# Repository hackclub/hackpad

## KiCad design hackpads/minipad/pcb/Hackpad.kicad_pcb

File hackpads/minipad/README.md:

# Minipad
My first time experimenting with PCB, keyboards, firmware and everything that comes along with it.
To keep things simple, I created a simple 4 switch grid (with one rotary encoder) direct wired to the microcontroller.
The case is another simple design, with a rectangular shape with curved corners, with some empty space to add some stickers or similar.

# BOM
- 3x Cherry MX switches
- 1x EC11 Encoder
- 1x PCB
- 1x Xiao Seeed RP2040
- 3x Blank DSA Key Caps
- 1x sticker to put on top

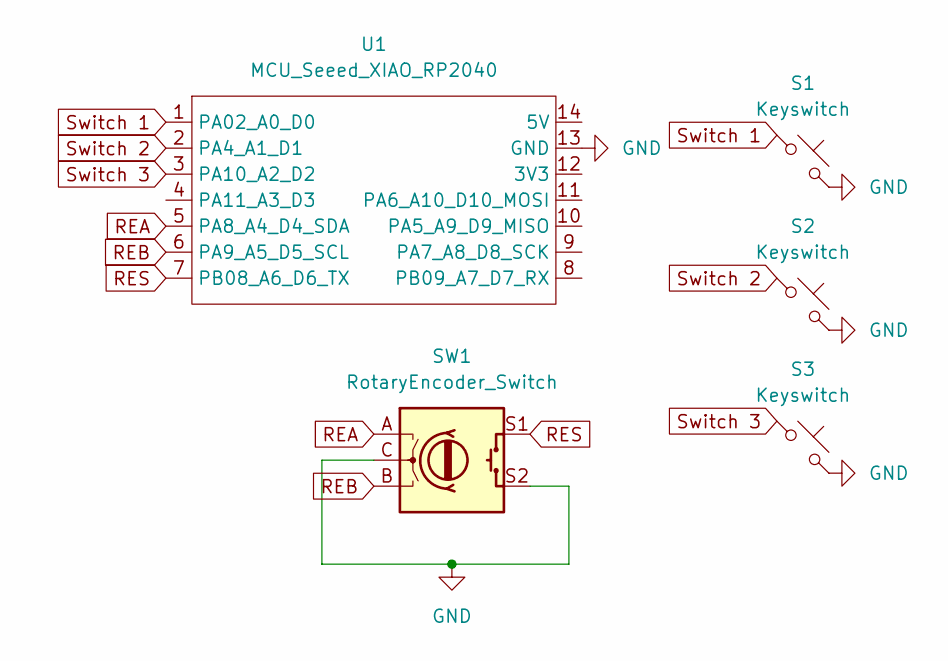
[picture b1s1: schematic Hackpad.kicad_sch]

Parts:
S1, S2, S3: Keyswitch; MX_PCB_1.00u
SW1: RotaryEncoder_Switch; Encoder_EC11_MX
U1: MCU_Seeed_XIAO_RP2040; Seeed_XIAO_RP2040

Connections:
GND: S1.2, S2.2, S3.2, SW1.C, SW1.S2, U1.13 (GND)
REA: SW1.A, U1.5 (PA8_A4_D4_SDA)
REB: SW1.B, U1.6 (PA9_A5_D5_SCL)
RES: SW1.S1, U1.7 (PB08_A6_D6_TX)
Switch 1: S1.1, U1.1 (PA02_A0_D0)
Switch 2: S2.1, U1.2 (PA4_A1_D1)
Switch 3: S3.1, U1.3 (PA10_A2_D2)

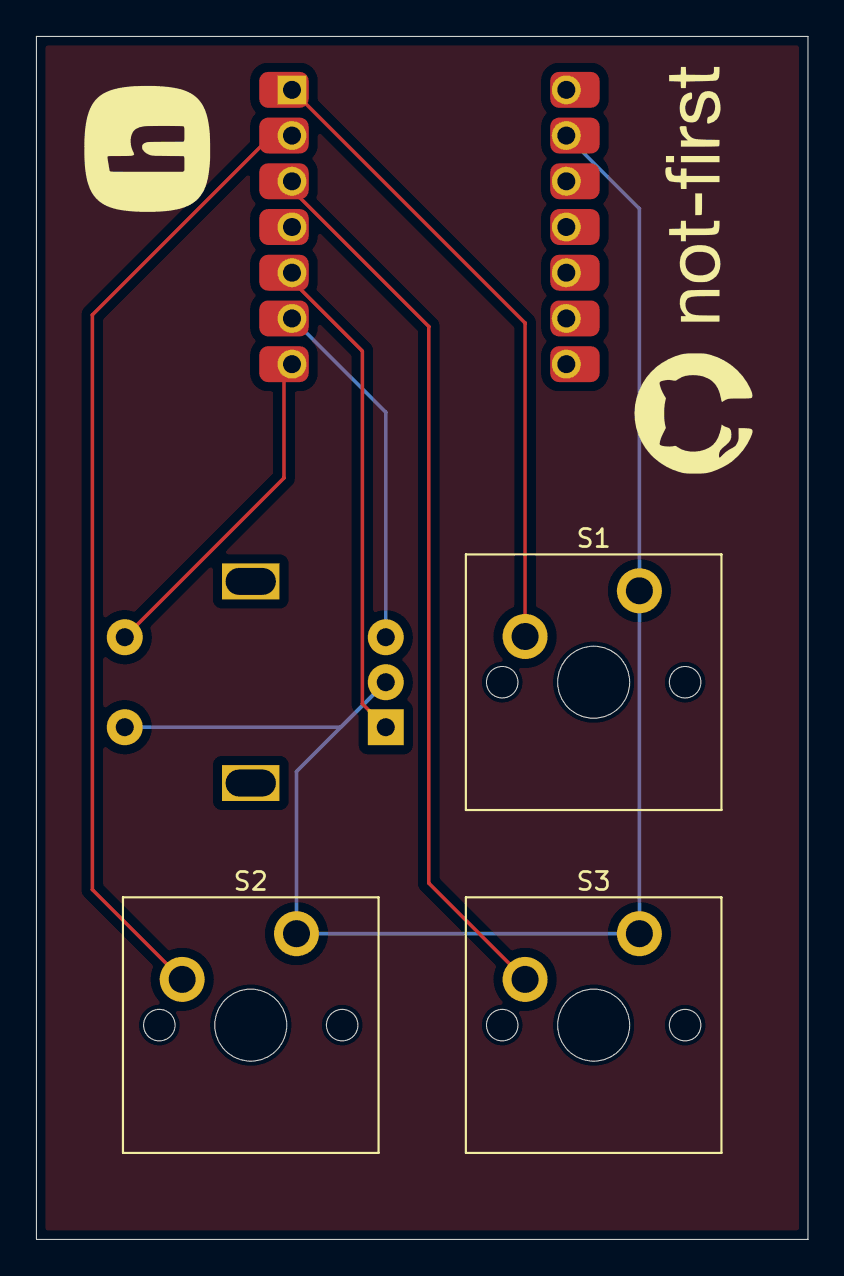
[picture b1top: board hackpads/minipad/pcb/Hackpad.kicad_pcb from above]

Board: 2 copper layers, 42.9 x 66.8 mm, 5 parts (0 on the bottom side), 7 nets.

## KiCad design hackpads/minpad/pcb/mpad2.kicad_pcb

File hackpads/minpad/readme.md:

# Minpad

A simple 2x3 macro pad with a display!

Designing a case was difficult, as I barely have any cad experience, but the PCB was really fun! I'll definitely look into more projects like this later on.

## PCB

Front and back of the PCB, the whole board uses a fill zone.

## Bill of materials

| Component                  | Amount |
|----------------------------|--------|
| PCB                        | 1      |
| Cherry MX Switches         | 6      |
| Seeduino Xiao RP2040       | 1      |
| WS28128 LED                | 1      |
| Through-hole 1N4148 Diodes | 6      |
| OLED 128x32                | 1      |
| Keycaps                    | 6      |

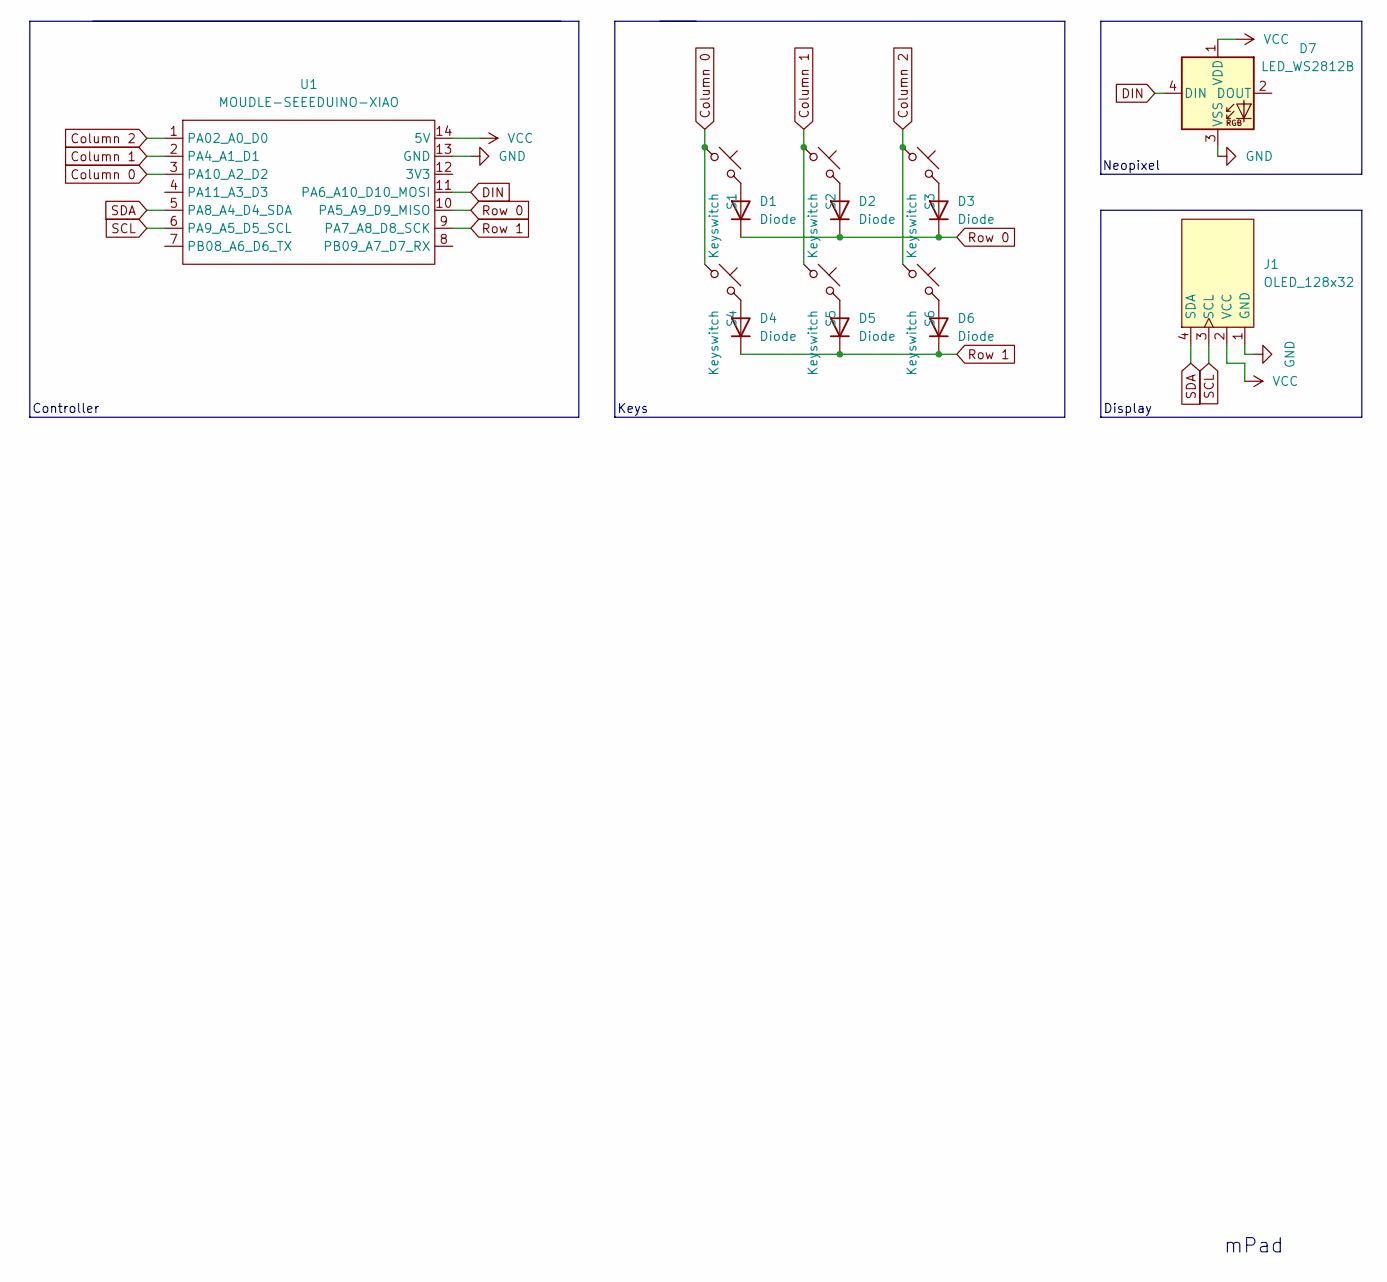
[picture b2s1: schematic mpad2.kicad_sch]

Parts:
D1, D2, D3, D4, D5, D6: Diode; Diode_DO-35
D7: LED_WS2812B
J1: OLED_128x32
S1, S2, S3, S4, S5, S6: Keyswitch; MX_PCB_1.00u
U1: MOUDLE-SEEEDUINO-XIAO; Seeed_XIAO_RP2040

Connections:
Column 0: S1.1, S4.1, U1.3 (PA10_A2_D2)
Column 1: S2.1, S5.1, U1.2 (PA4_A1_D1)
Column 2: S3.1, S6.1, U1.1 (PA02_A0_D0)
DIN: D7.4 (DIN), U1.11 (PA6_A10_D10_MOSI)
GND: D7.3 (VSS), J1.1 (GND), U1.13 (GND)
unnamed: D1.2 (A), S1.2
unnamed: D2.2 (A), S2.2
unnamed: D3.2 (A), S3.2
unnamed: D4.2 (A), S4.2
unnamed: D5.2 (A), S5.2
unnamed: D6.2 (A), S6.2
Row 0: D1.1 (K), D2.1 (K), D3.1 (K), U1.10 (PA5_A9_D9_MISO)
Row 1: D4.1 (K), D5.1 (K), D6.1 (K), U1.9 (PA7_A8_D8_SCK)
SCL: J1.3 (SCL), U1.6 (PA9_A5_D5_SCL)
SDA: J1.4 (SDA), U1.5 (PA8_A4_D4_SDA)
VCC: D7.1 (VDD), J1.2 (VCC), U1.14 (5V)

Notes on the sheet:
Neopixel
Controller
mPad
Display
Keys

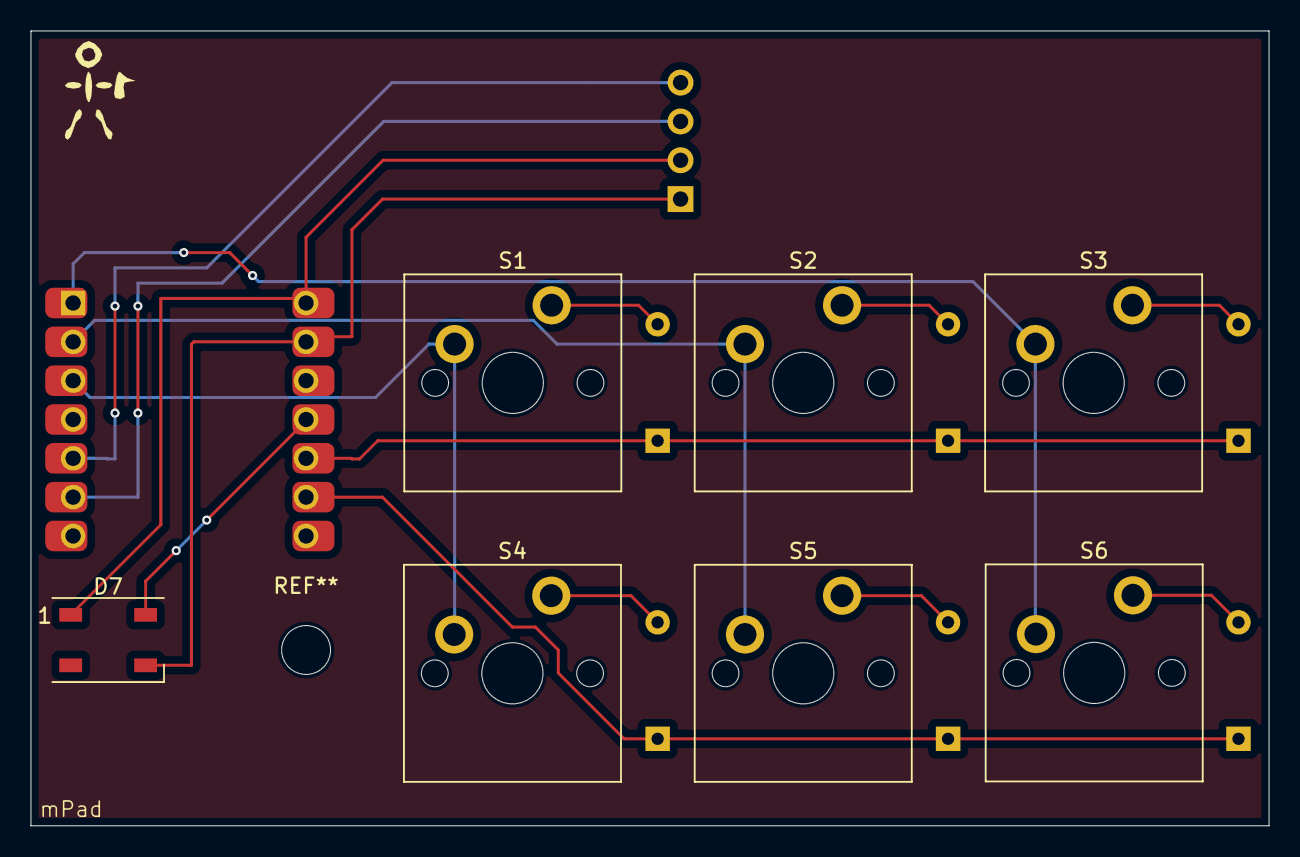
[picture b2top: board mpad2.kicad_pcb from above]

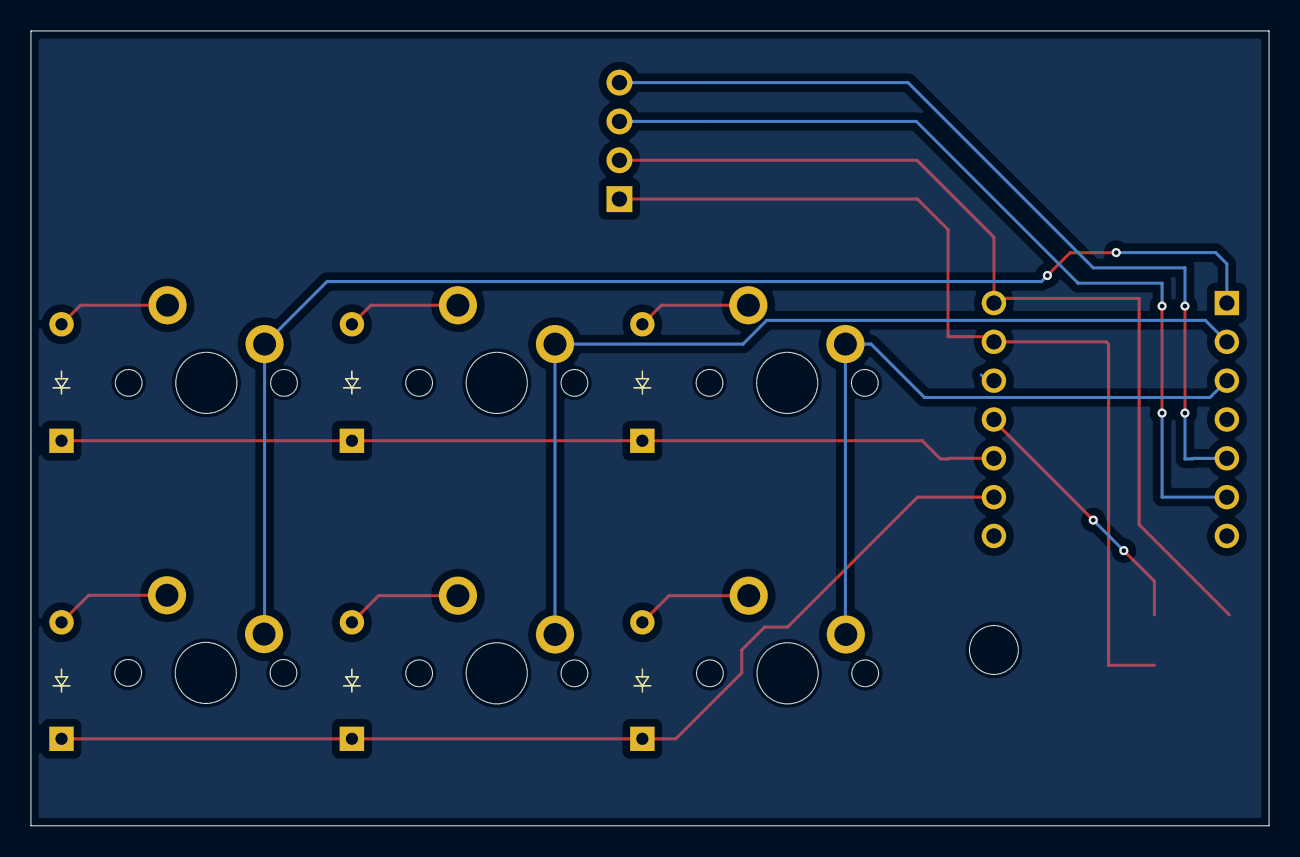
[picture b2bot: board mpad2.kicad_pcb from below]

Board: 2 copper layers, 81.0 x 52.0 mm, 15 parts (6 on the bottom side), 16 nets.

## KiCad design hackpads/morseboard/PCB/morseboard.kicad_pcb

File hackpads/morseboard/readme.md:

# Morseboard

My hackpad keyboard is a keyboard that types in morse code. The rotary encoder is for volume. I was inspired to do this because I kept making smaller and smaller keyboards, and this is the next step in my journey. Maybe one day, I'll make a 1-key keyboard. The reason I chose to use morse code, was because I coincidentally was learning it for fun. This was also my first time truly designing my own keyboard with my previous keyboards just being half of a pre-built split keyboard, so I had to learn how to use real CAD tools.

## Features
- Rotary Encoder
- Morse Code!!
- Screen

## Schematics

## PCB

## Assembly

## BOM

| Qty | Part Name               |
|-----|-------------------------|
| 1   | Rotary Encoder          |
| 6   | Cherry MX Switches      |
| 6   | DSA Keycaps             |
| 1   | 0.91 inch OLED displays |
| 7   | SK6812 MINI-E LEDs      |
| 1   | Seeed XIAO RP2040       |
| 6   | THT 1N4148 Diodes       |
| 1   | Case (3d-printed)       |
| 5   | PCB                     |

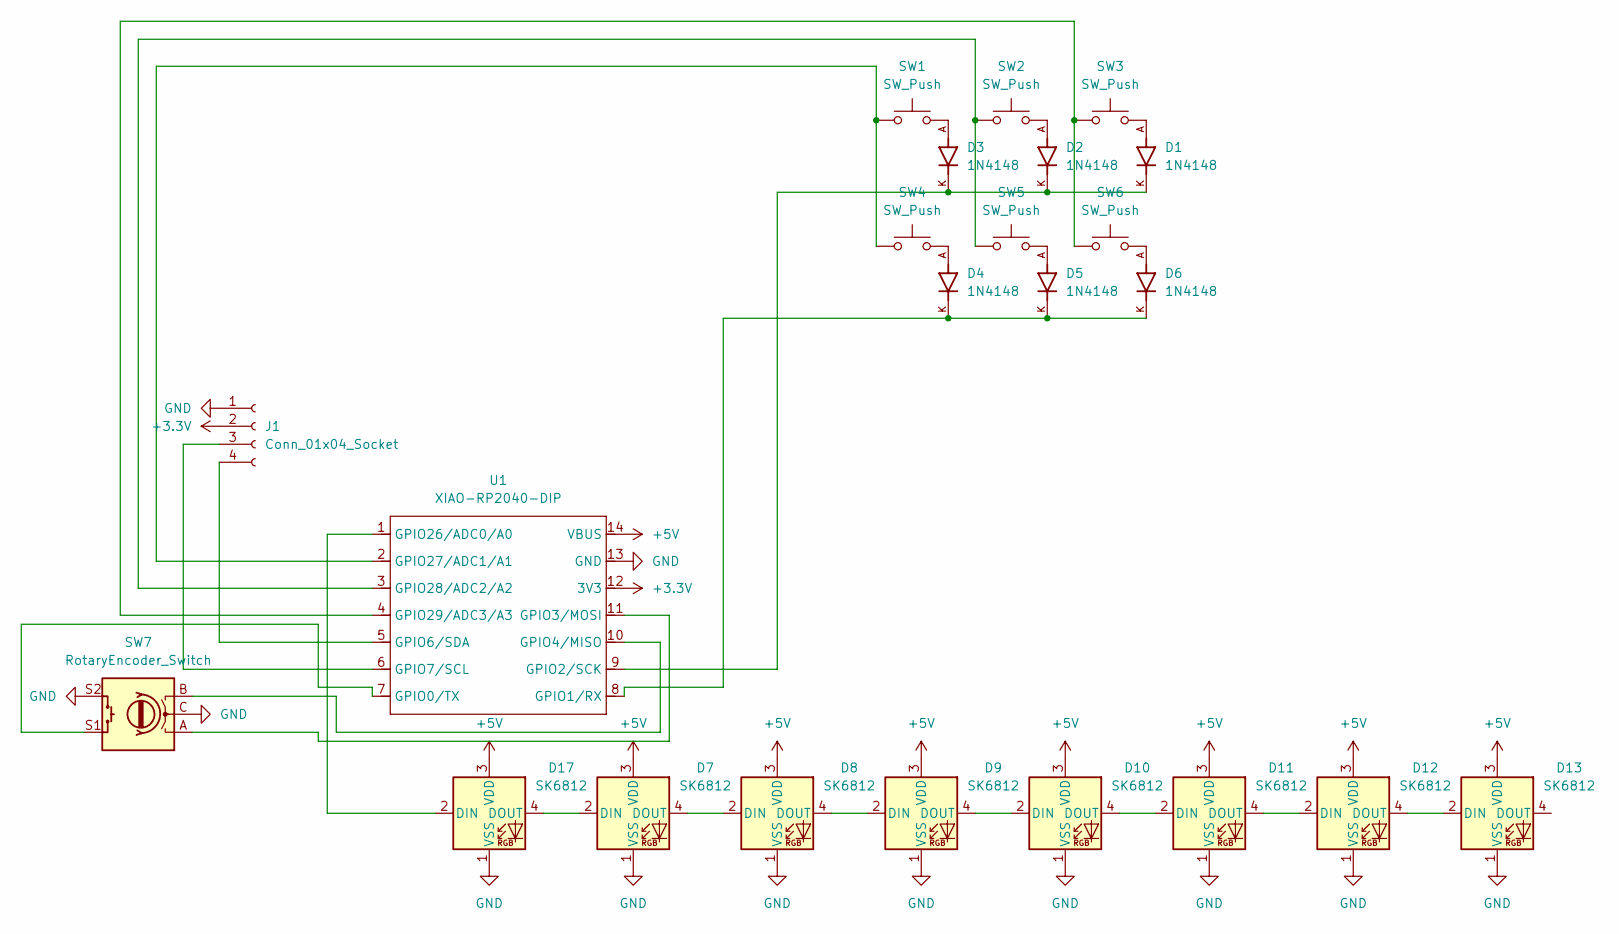
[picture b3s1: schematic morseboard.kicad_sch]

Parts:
D1, D2, D3, D4, D5, D6: 1N4148; DIOAD753W49L380D172B; PARTREV 5; DigiKey_Part_Number 1N4148FS-ND
D7, D8, D9, D10, D11, D12, D13, D17: SK6812; LED_SK6812_PLCC4_5.0x5.0mm_P3.2mm
J1: Conn_01x04_Socket; SSD1306-0.91-OLED-4pin-128x32
SW1, SW2, SW3, SW4, SW5, SW6: SW_Push; SW_Cherry_MX_1.00u_PCB
SW7: RotaryEncoder_Switch; RotaryEncoder_Alps_EC11E-Switch_Vertical_H20mm_CircularMoun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
U1: XIAO-RP2040-DIP

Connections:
+3.3V: J1.2, U1.12 (3V3)
+5V: D7.3 (VDD), D8.3 (VDD), D9.3 (VDD), D10.3 (VDD), D11.3 (VDD), D12.3 (VDD), D13.3 (VDD), D17.3 (VDD), U1.14 (VBUS)
GND: D7.1 (VSS), D8.1 (VSS), D9.1 (VSS), D10.1 (VSS), D11.1 (VSS), D12.1 (VSS), D13.1 (VSS), D17.1 (VSS), J1.1, SW7.C, SW7.S2, U1.13 (GND)
unnamed: D1.A, SW3.2
unnamed: D2.A, SW2.2
unnamed: D3.A, SW1.2
unnamed: D4.A, SW4.2
unnamed: D5.A, SW5.2
unnamed: D6.A, SW6.2
unnamed: D7.4 (DOUT), D8.2 (DIN)
unnamed: D8.4 (DOUT), D9.2 (DIN)
unnamed: D9.4 (DOUT), D10.2 (DIN)
unnamed: D10.4 (DOUT), D11.2 (DIN)
unnamed: D11.4 (DOUT), D12.2 (DIN)
unnamed: D12.4 (DOUT), D13.2 (DIN)
unnamed: D17.2 (DIN), U1.1 (GPIO26/ADC0/A0)
unnamed: D7.2 (DIN), D17.4 (DOUT)
unnamed: J1.3, U1.6 (GPIO7/SCL)
unnamed: J1.4, U1.5 (GPIO6/SDA)
unnamed: SW7.S1, U1.7 (GPIO0/TX)
unnamed: D4.K, D5.K, D6.K, U1.8 (GPIO1/RX)
unnamed: D1.K, D2.K, D3.K, U1.9 (GPIO2/SCK)
unnamed: SW7.A, U1.11 (GPIO3/MOSI)
unnamed: SW7.B, U1.10 (GPIO4/MISO)
unnamed: SW1.1, SW4.1, U1.2 (GPIO27/ADC1/A1)
unnamed: SW2.1, SW5.1, U1.3 (GPIO28/ADC2/A2)
unnamed: SW3.1, SW6.1, U1.4 (GPIO29/ADC3/A3)

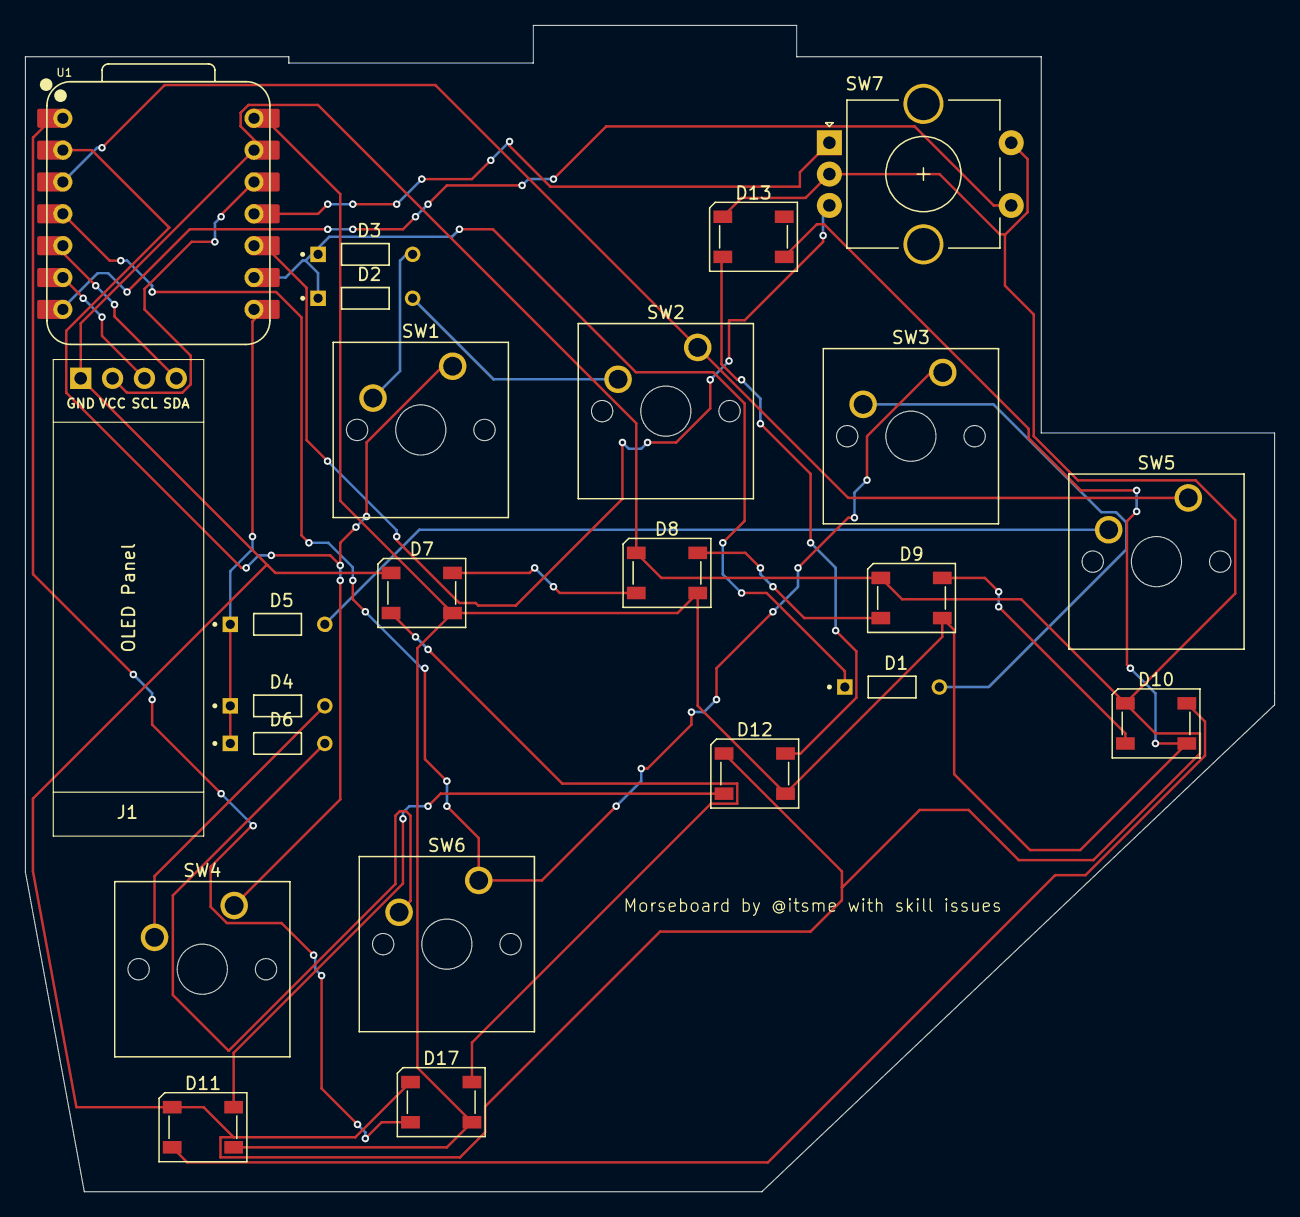
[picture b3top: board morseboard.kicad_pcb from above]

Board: 2 copper layers, 99.6 x 93.0 mm, 23 parts (0 on the bottom side), 27 nets.

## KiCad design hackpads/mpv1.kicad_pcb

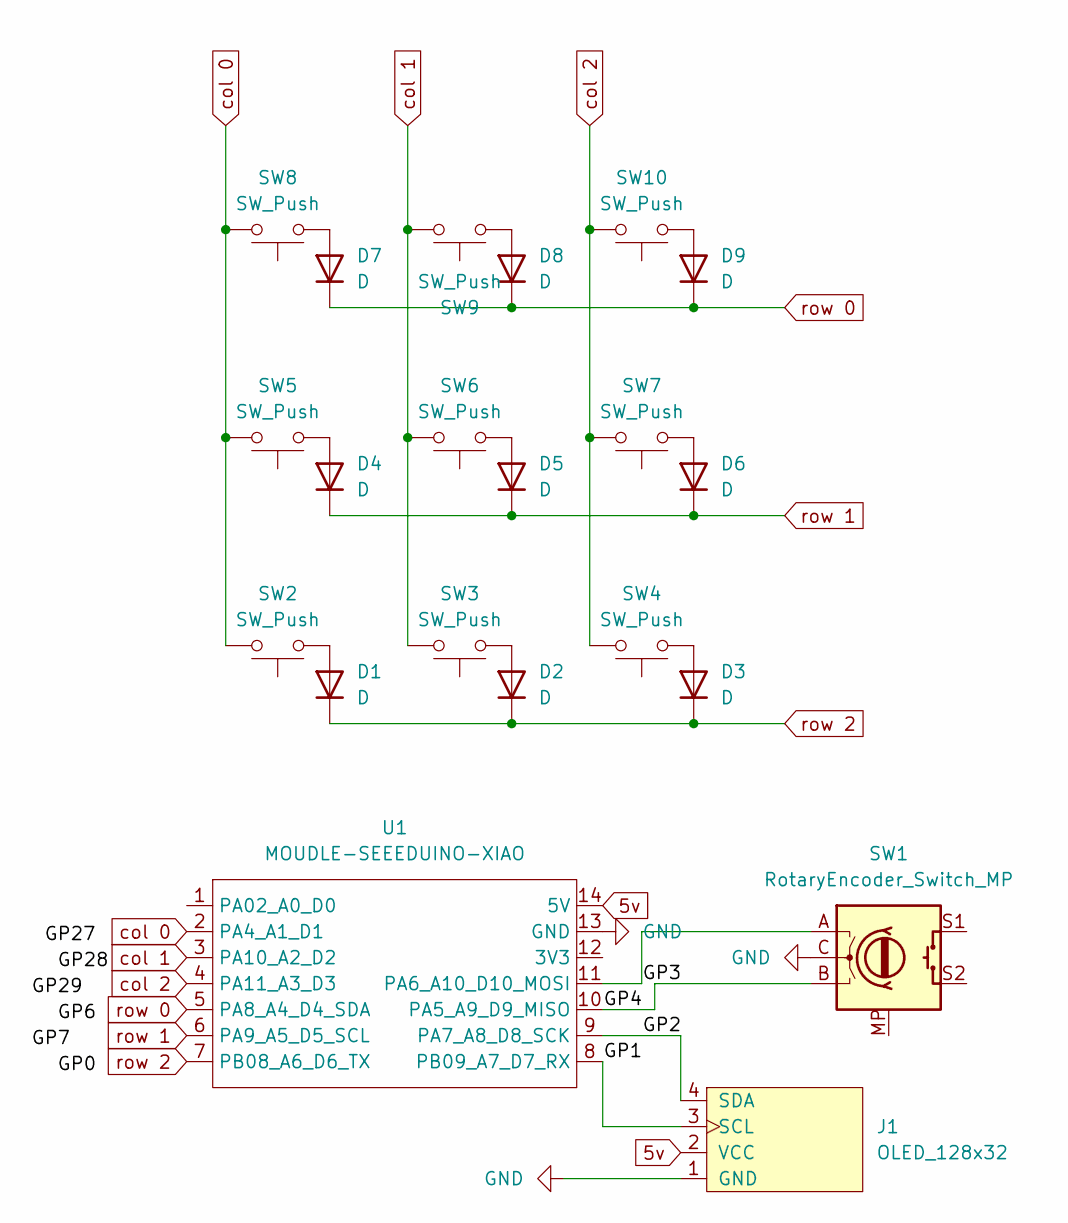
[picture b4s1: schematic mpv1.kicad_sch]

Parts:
D1, D2, D3, D4, D5, D6, D7, D8, D9: D; Diode_DO-35
J1: OLED_128x32; SSD1306-0.91-OLED-4pin-128x32
SW1: RotaryEncoder_Switch_MP; Encoder_EC11_MX
SW2, SW3, SW4, SW5, SW6, SW7, SW8, SW9, SW10: SW_Push; SW_Cherry_MX_1.00u_PCB
U1: MOUDLE-SEEEDUINO-XIAO; XIAO-Generic-Hybrid-14P-2.54-21X17.8MM

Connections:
5v: J1.2 (VCC), U1.14 (5V); also elsewhere on the board
GND: J1.1 (GND), SW1.C, U1.13 (GND); also elsewhere on the board
unnamed: D1.2 (A), SW2.1
unnamed: D2.2 (A), SW3.1
unnamed: D3.2 (A), SW4.1
unnamed: D4.2 (A), SW5.1
unnamed: D5.2 (A), SW6.1
unnamed: D6.2 (A), SW7.1
unnamed: D7.2 (A), SW8.1
unnamed: D8.2 (A), SW9.1
unnamed: D9.2 (A), SW10.1
unnamed 11: J1.3 (SCL), U1.8 (PB09_A7_D7_RX); also elsewhere on the board
unnamed 12: J1.4 (SDA), U1.9 (PA7_A8_D8_SCK); also elsewhere on the board
unnamed: SW1.B, U1.10 (PA5_A9_D9_MISO)
unnamed: SW1.A, U1.11 (PA6_A10_D10_MOSI)
col 0: SW2.2, SW5.2, SW8.2, U1.2 (PA4_A1_D1)
col 1: SW3.2, SW6.2, SW9.2, U1.3 (PA10_A2_D2)
col 2: SW4.2, SW7.2, SW10.2, U1.4 (PA11_A3_D3)
row 0: D7.1 (K), D8.1 (K), D9.1 (K), U1.5 (PA8_A4_D4_SDA)
row 1: D4.1 (K), D5.1 (K), D6.1 (K), U1.6 (PA9_A5_D5_SCL)
row 2: D1.1 (K), D2.1 (K), D3.1 (K), U1.7 (PB08_A6_D6_TX)

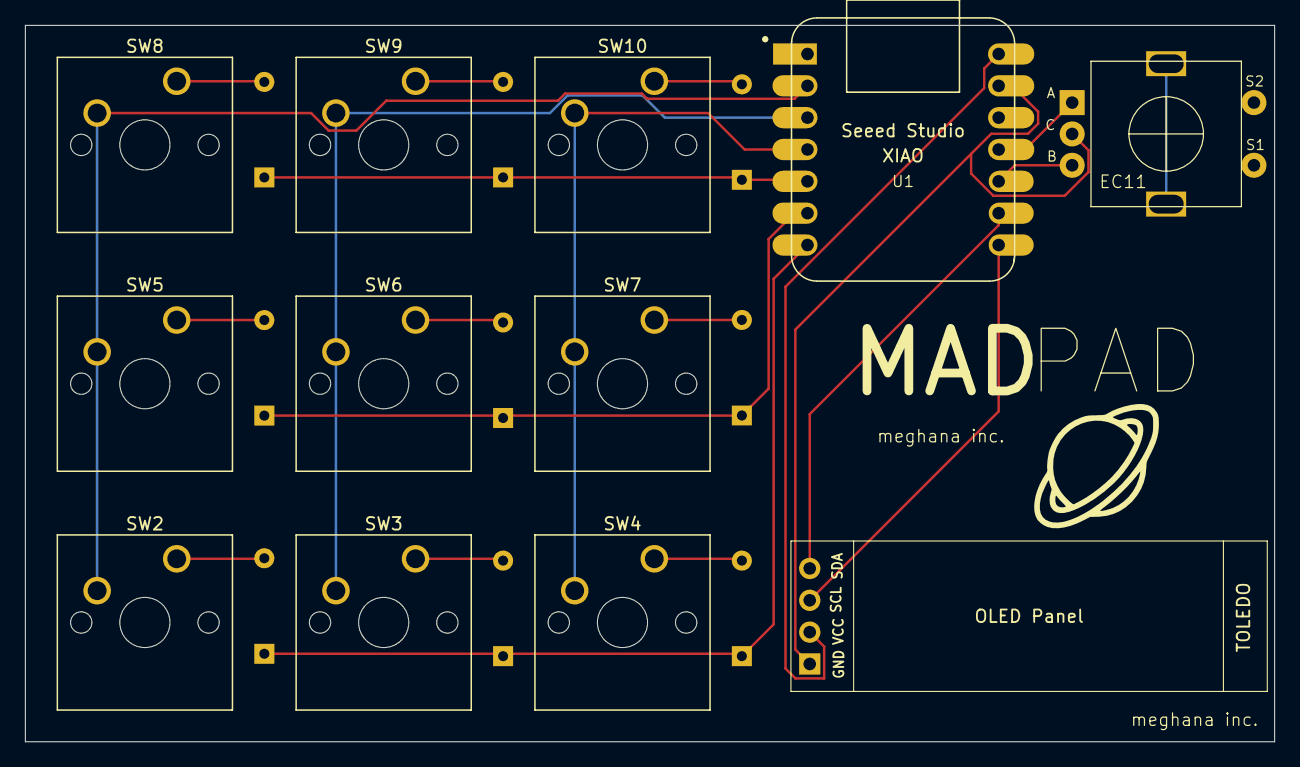
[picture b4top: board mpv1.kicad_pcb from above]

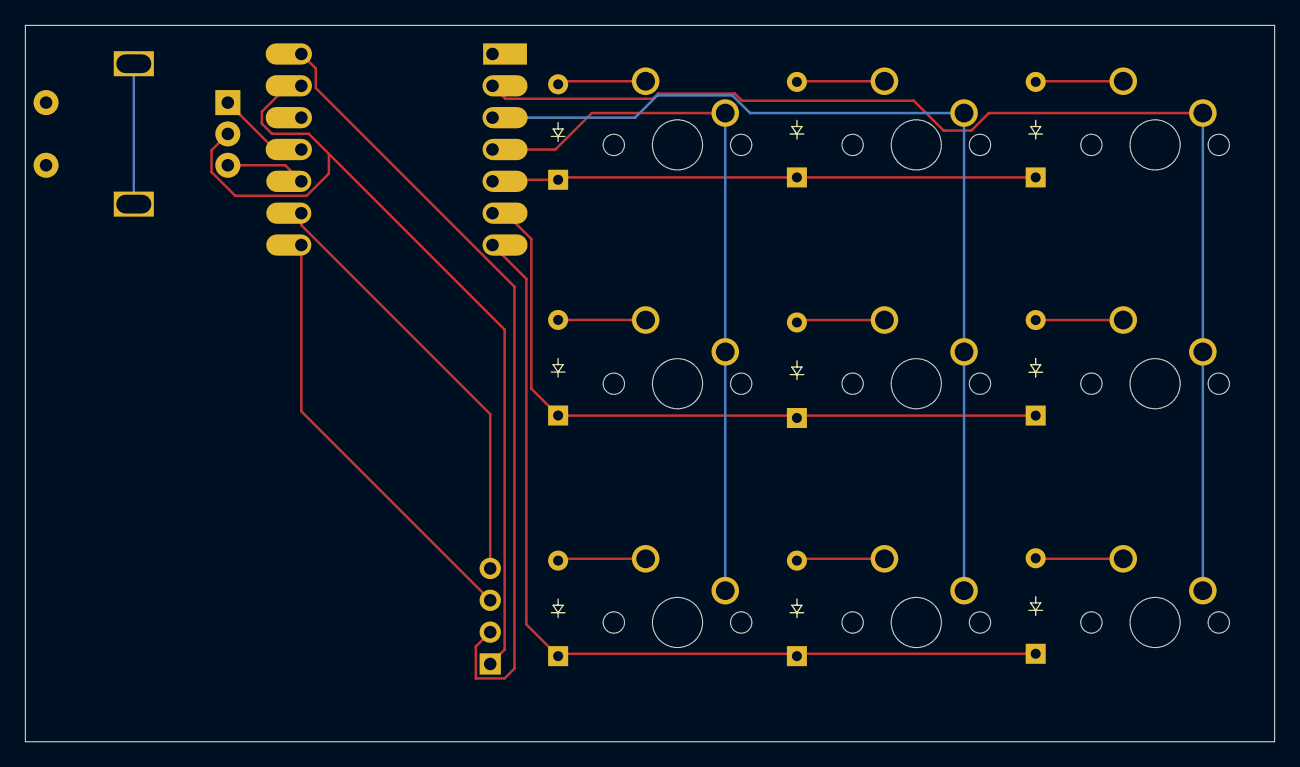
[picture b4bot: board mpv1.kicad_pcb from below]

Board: 2 copper layers, 99.7 x 57.2 mm, 21 parts (9 on the bottom side), 21 nets.

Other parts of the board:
TOLEDO: OLED_128x32; SSD1306-0.91-OLED-4pin-128x32

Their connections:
5v: TOLEDO.2 (VCC); also elsewhere on the board
GND: TOLEDO.1 (GND); also elsewhere on the board
unnamed 11: TOLEDO.3 (SCL); also elsewhere on the board
unnamed 12: TOLEDO.4 (SDA); also elsewhere on the board

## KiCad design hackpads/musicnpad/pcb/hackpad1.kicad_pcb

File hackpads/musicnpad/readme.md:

# musicnpad

A 16 key modified numpad with a 32x128 OLED.

## Why?

I was frustrated completing math/science homework online, having to type in so many numbers. I designed this numpad to allow me to type numbers quickly, tab between input fields, and control music while I work.

## BOM:
- 1x PCB
- 16x MX Switches
- 16x through-hole diode
- 1x Speed XIAO RP2040
- 1x case top (3d printed)
- 1x case bottom (3d printed)\
- 2x 2.0u key stabilizer
- 1x 0.91in 128x32px I2C OLED display

## Hardest Challenge

I had experience with electronic circuits and CAD before, but I had never designed a circuit board. That presented a bit of a learning curve. I found myself becoming too much of a perfectionist with the PCB design. Everything was fairly straightforward until I got to compiling QMK, which took a bit of guesswork. Nothing was super difficult, just a lot of learning experiences.

## Schematic:

## PCB

## Case

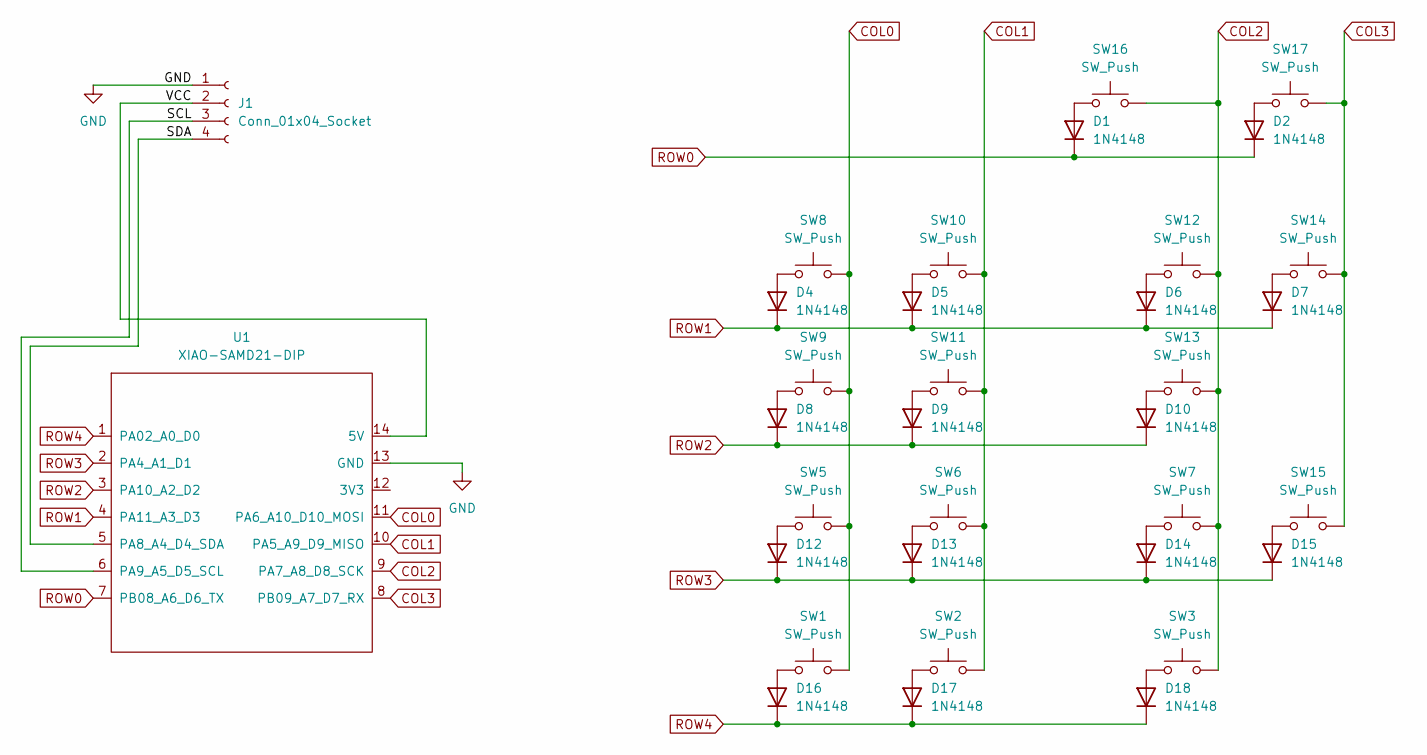
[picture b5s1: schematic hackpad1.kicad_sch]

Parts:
D1, D2, D4, D5, D6, D7, D8, D9, D10, D12, D13, D14, D15, D16, D17, D18: 1N4148; D_DO-35_SOD27_P7.62mm_Horizontal
J1: Conn_01x04_Socket; SSD1306-0.91-OLED-4pin-128x32
SW1, SW2, SW3, SW5, SW6, SW7, SW8, SW9, SW10, SW11, SW12, SW13, SW16, SW17: SW_Push; SW_Cherry_MX_1.00u_PCB
SW14, SW15: SW_Push; SW_Cherry_MX_2.00u_Vertical_PCB
U1: XIAO-SAMD21-DIP

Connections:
/SCL: J1.3, U1.6 (PA9_A5_D5_SCL)
/SDA: J1.4, U1.5 (PA8_A4_D4_SDA)
/VCC: J1.2, U1.14 (5V)
COL0: SW1.2, SW5.2, SW8.2, SW9.2, U1.11 (PA6_A10_D10_MOSI)
COL1: SW2.2, SW6.2, SW10.2, SW11.2, U1.10 (PA5_A9_D9_MISO)
COL2: SW3.2, SW7.2, SW12.2, SW13.2, SW16.2, U1.9 (PA7_A8_D8_SCK)
COL3: SW14.2, SW15.2, SW17.2, U1.8 (PB09_A7_D7_RX)
GND: J1.1, U1.13 (GND)
unnamed: D1.2 (A), SW16.1
unnamed: D2.2 (A), SW17.1
unnamed: D4.2 (A), SW8.1
unnamed: D5.2 (A), SW10.1
unnamed: D6.2 (A), SW12.1
unnamed: D7.2 (A), SW14.1
unnamed: D8.2 (A), SW9.1
unnamed: D9.2 (A), SW11.1
unnamed: D10.2 (A), SW13.1
unnamed: D12.2 (A), SW5.1
unnamed: D13.2 (A), SW6.1
unnamed: D14.2 (A), SW7.1
unnamed: D15.2 (A), SW15.1
unnamed: D16.2 (A), SW1.1
unnamed: D17.2 (A), SW2.1
unnamed: D18.2 (A), SW3.1
ROW0: D1.1 (K), D2.1 (K), U1.7 (PB08_A6_D6_TX)
ROW1: D4.1 (K), D5.1 (K), D6.1 (K), D7.1 (K), U1.4 (PA11_A3_D3)
ROW2: D8.1 (K), D9.1 (K), D10.1 (K), U1.3 (PA10_A2_D2)
ROW3: D12.1 (K), D13.1 (K), D14.1 (K), D15.1 (K), U1.2 (PA4_A1_D1)
ROW4: D16.1 (K), D17.1 (K), D18.1 (K), U1.1 (PA02_A0_D0)

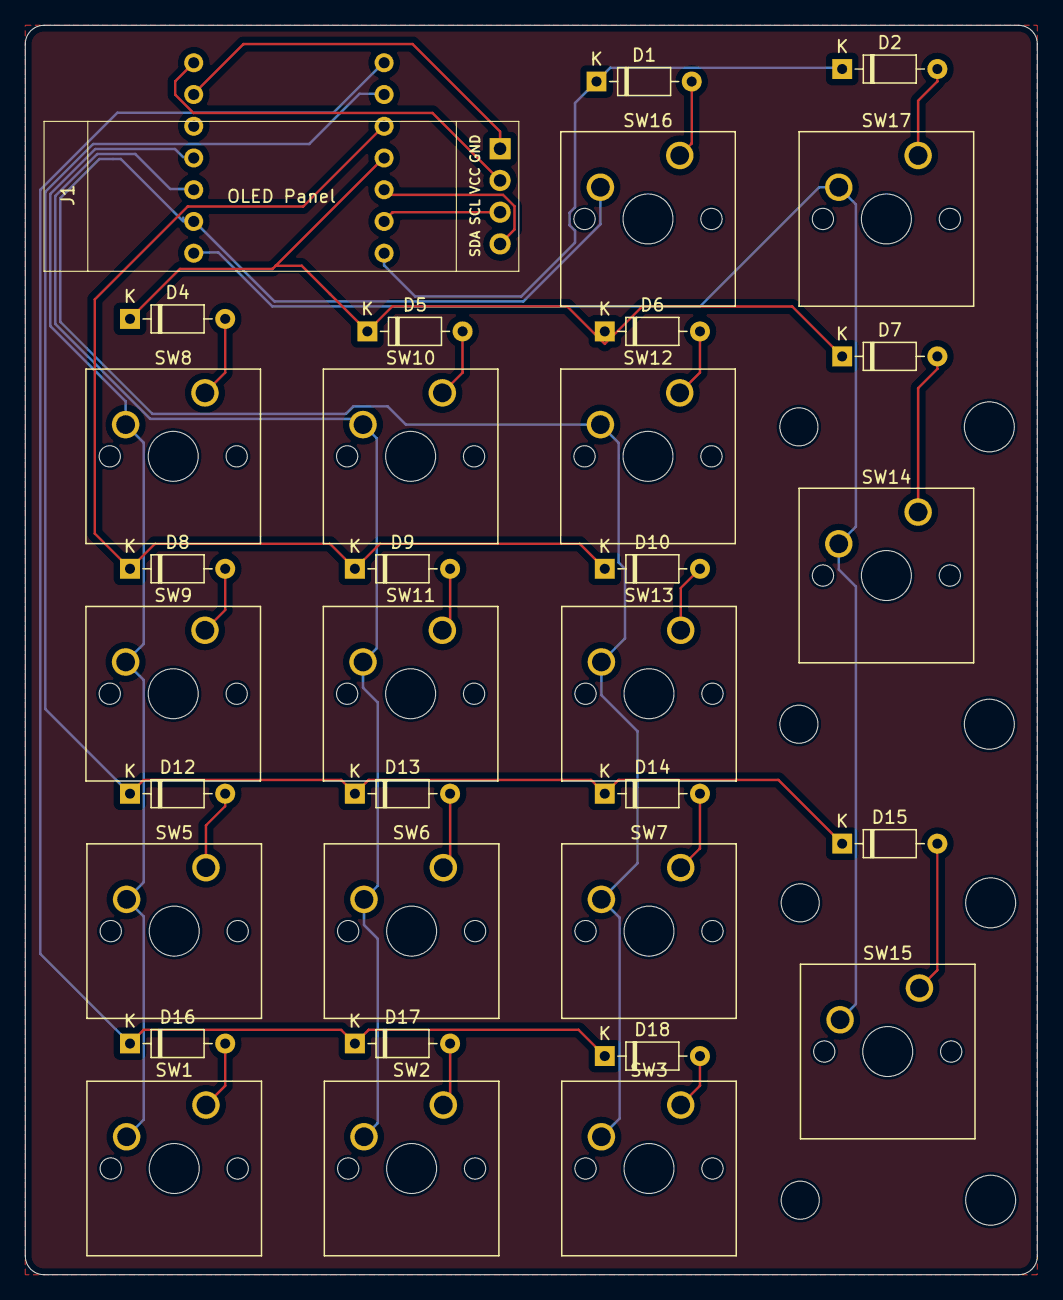
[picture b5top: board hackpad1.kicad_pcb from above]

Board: 2 copper layers, 81.0 x 100.0 mm, 34 parts (1 on the bottom side), 29 nets.

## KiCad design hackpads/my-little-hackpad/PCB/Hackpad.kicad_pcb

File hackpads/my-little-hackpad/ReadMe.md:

# Read Me of my little hackpad
## Inspiration for me
- A little Project to make school more fun
- Have a challenge

## Hardest Part
- CAD Design

## Learn something new
- PCB Design
- Case Design
- Wirte your own firmware

## BOM: Material needed for one Pad
- 1x PCB Board
- 1x Seeed XIAO RP2024
- 1x Esp8266
- 4x WS2812B
- 1x 0.91 inch OLED Display
- 1x EC11 Rotary Encoder
- 9x Cherry MX switches
- 4x Heatsets
- 4x Screws M3 16mm

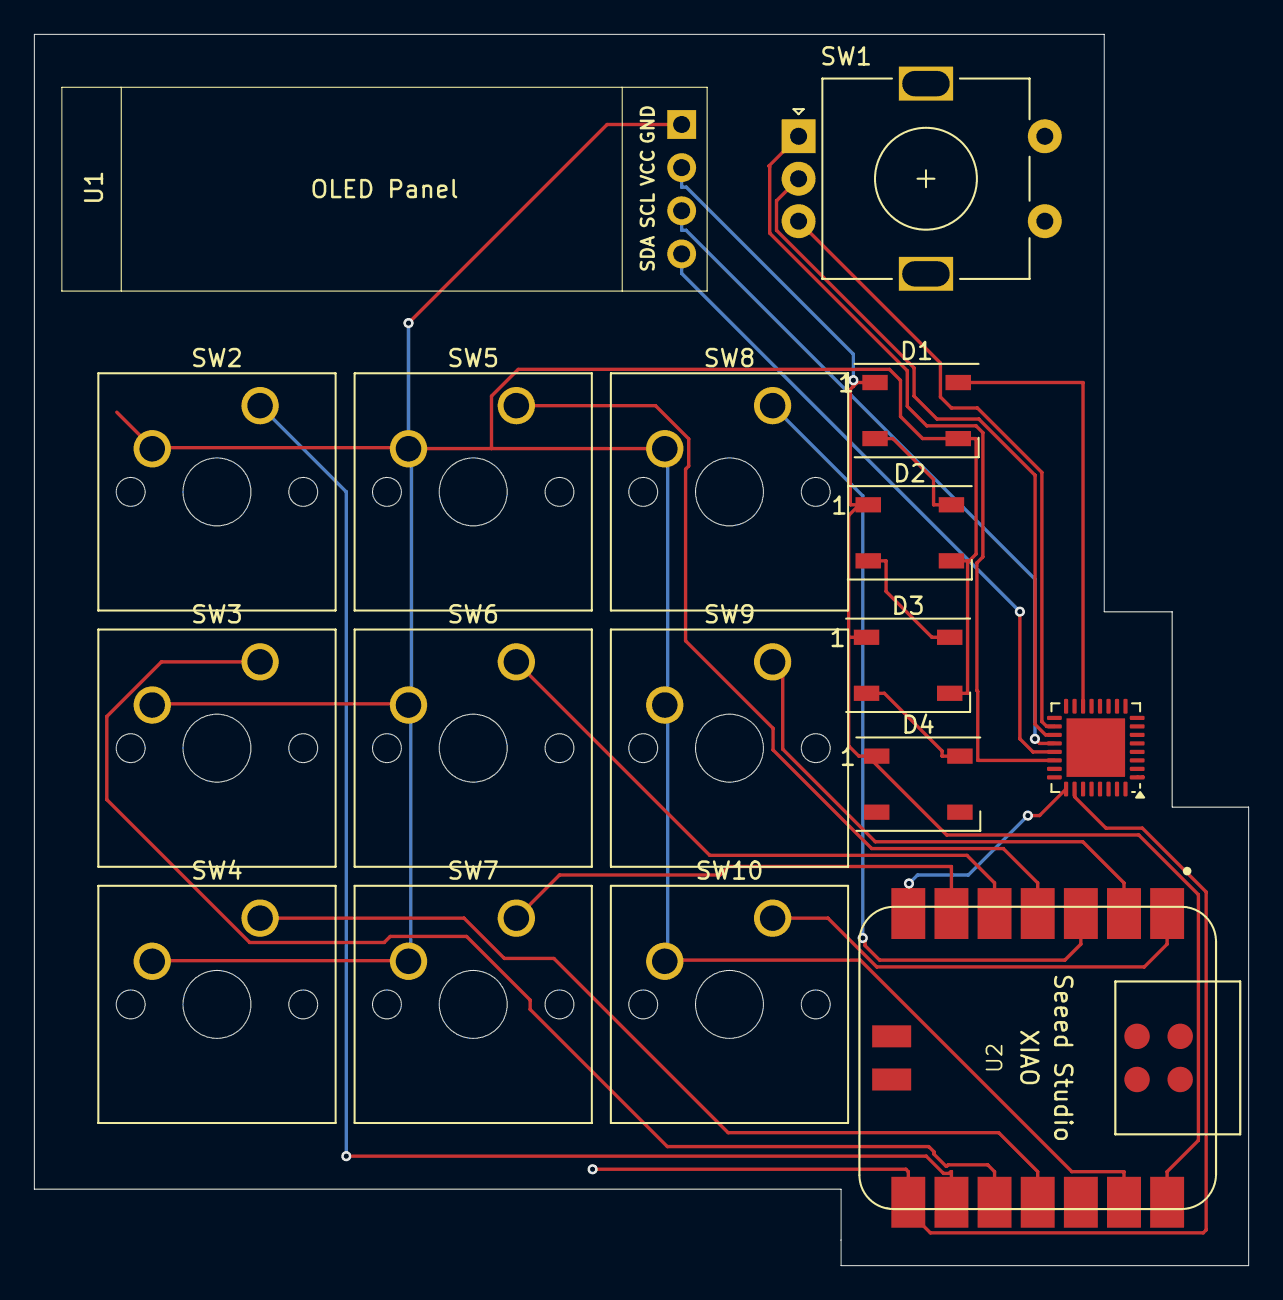
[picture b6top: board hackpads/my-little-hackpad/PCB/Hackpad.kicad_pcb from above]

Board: 2 copper layers, 71.5 x 72.5 mm, 17 parts (0 on the bottom side), 22 nets.

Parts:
D1, D2, D3, D4: WS2812B; LED_WS2812B_PLCC4_5.0x5.0mm_P3.2mm
SW1: RotaryEncoder_Switch; RotaryEncoder_Alps_EC11E-Switch_Vertical_H20mm
SW2, SW3, SW4, SW5, SW6, SW7, SW8, SW9, SW10: SW_Push; SW_Cherry_MX_1.00u_PCB
U1: SSD1306-0.91-OLED-4pin-128x32
U2: Seeed Studio XIAO SAMD21; XIAO-SAMD21-RP2040-14P-2.54-21X17.8MM (Seeeduino XIAO)
U3: ESP8266EX; QFN-32-1EP_5x5mm_P0.5mm_EP3.45x3.45mm

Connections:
GND: D1.3 (VSS), D2.3 (VSS), D3.3 (VSS), SW2.2, SW3.2, SW4.2, SW5.2, SW6.2, SW7.2, SW8.2, SW9.2, SW10.2, U1.1 (GND), U2.13 (GND)
unnamed: D1.4 (DIN), U3.14 (GPIO2)
unnamed: D1.2 (DOUT), D2.4 (DIN)
unnamed: D1.1 (VDD), D2.1 (VDD), D3.1 (VDD), D4.1 (VDD), U1.2 (VCC), U2.14 (5V)
unnamed: D2.2 (DOUT), D3.4 (DIN)
unnamed: D3.2 (DOUT), D4.4 (DIN)
unnamed: U1.3 (SCL), U3.20 (SDIO_CMD)
unnamed: U1.4 (SDA), U3.21 (SDIO_CLK)
unnamed: SW10.1, U2.1 (PA02_A0_D0)
unnamed: SW9.1, U2.2 (PA4_A1_D1)
unnamed: SW3.1, U2.10 (PA5_A9_D9_MISO)
unnamed: SW4.1, U2.11 (PA6_A10_D10_MOSI)
unnamed: SW2.1, U2.9 (PA7_A8_D8_SCK)
unnamed: SW6.1, U2.5 (PA8_A4_D4_SDA)
unnamed: SW7.1, U2.6 (PA9_A5_D5_SCL)
unnamed: SW8.1, U2.3 (PA10_A2_D2)
unnamed: SW5.1, U2.4 (PA11_A3_D3)
unnamed: U2.7 (PB08_A6_D6_TX), U3.25 (U0RXD)
unnamed: U2.8 (PB09_A7_D7_RX), U3.26 (U0TXD)
unnamed: SW1.A, U3.22 (SDIO_DATA_0)
unnamed: SW1.B, U3.18 (SDIO_DATA_2)
unnamed: SW1.C, U3.19 (SDIO_DATA_3)
